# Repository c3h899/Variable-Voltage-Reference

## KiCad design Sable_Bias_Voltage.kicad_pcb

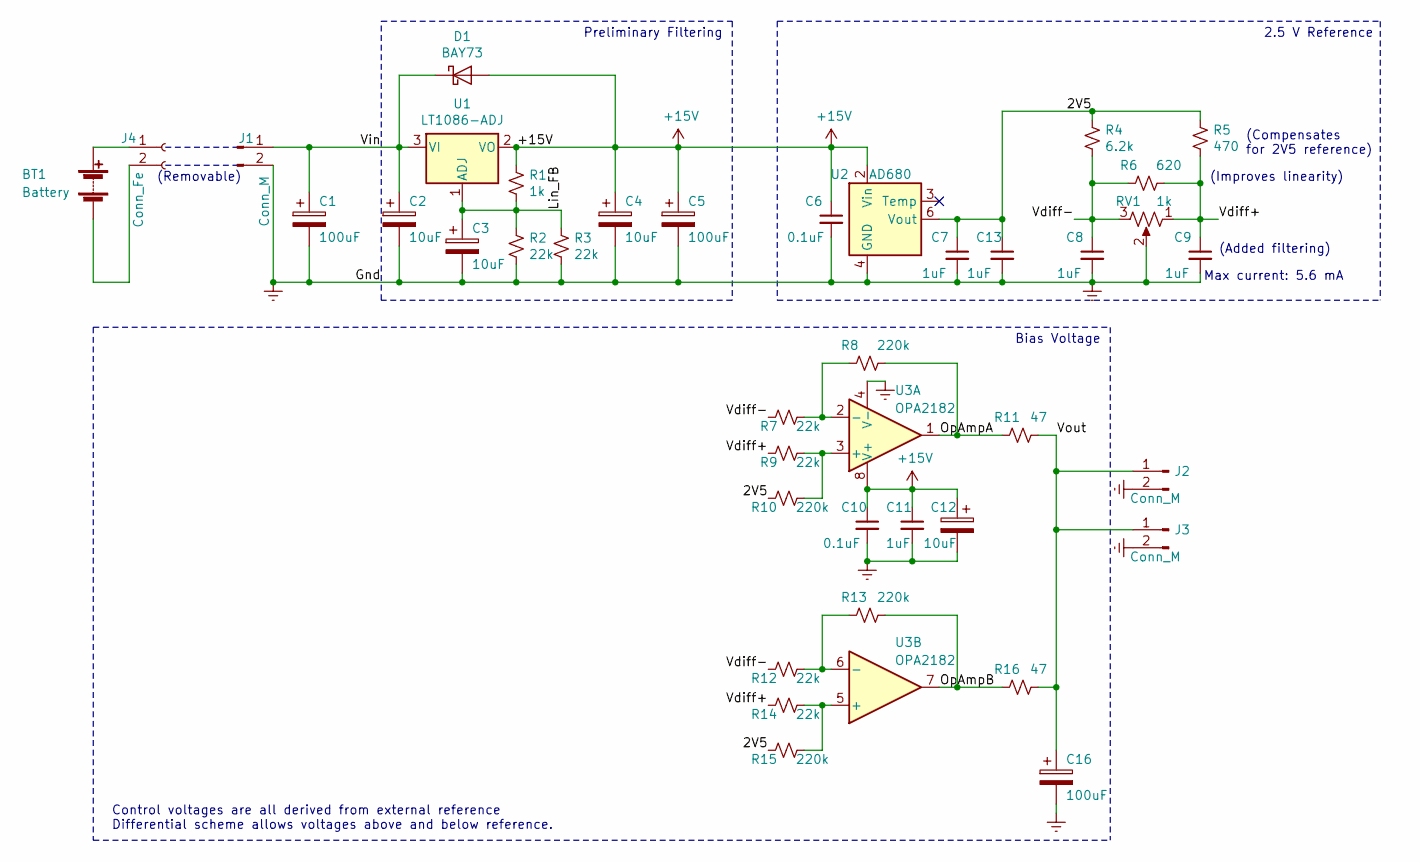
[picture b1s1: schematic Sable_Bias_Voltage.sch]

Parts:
BT1: Battery
C1, C5, C16: 100uF; CP_Radial_D8.0mm_P3.50mm
C2, C3, C4, C12: 10uF; C_Disc_D6.0mm_W4.4mm_P5.00mm
C6, C10: 0.1uF; C_Disc_D6.0mm_W2.5mm_P5.00mm
C7, C8, C9, C11, C13: 1uF; C_Disc_D6.0mm_W2.5mm_P5.00mm
D1: BAY73; D_DO-35_SOD27_P7.62mm_Horizontal
J1, J2, J3: Conn_M; PinHeader_1x02_P2.54mm_Vertical
J4: Conn_Fe
R1: 1k; R_Axial_DIN0204_L3.6mm_D1.6mm_P7.62mm_Horizontal
R2, R3, R7, R9, R12, R14: 22k; R_Axial_DIN0204_L3.6mm_D1.6mm_P7.62mm_Horizontal
R4: 6.2k; R_Axial_DIN0204_L3.6mm_D1.6mm_P7.62mm_Horizontal
R5: 470; R_Axial_DIN0204_L3.6mm_D1.6mm_P7.62mm_Horizontal
R6: 620; R_Axial_DIN0204_L3.6mm_D1.6mm_P7.62mm_Horizontal
R8, R10, R13, R15: 220k; R_Axial_DIN0204_L3.6mm_D1.6mm_P7.62mm_Horizontal
R11, R16: 47; R_Axial_DIN0204_L3.6mm_D1.6mm_P7.62mm_Horizontal
RV1: 1k; Potentiometer_Bourns_3266W_Vertical
U1: LT1086-ADJ; TO-220-3_Vertical
U2: AD680; DIP-8_W7.62mm_LongPads
U3: OPA2182; SOIC-8_3.9x4.9mm_P1.27mm

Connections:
+15V: C4.1, C5.1, C6.1, C10.1, C11.1, C12.1, D1.2 (A), R1.1, U1.2 (VO), U2.2 (Vin), U3.8 (V+)
/2V5: C7.1, C13.1, R4.1, R5.1, R10.2, R15.2, U2.6 (Vout)
/Lin_FB: C3.1, R1.2, R2.1, R3.1, U1.1 (ADJ)
/OpAmpA: R8.1, R11.2, U3.1
/OpAmpB: R13.1, R16.2, U3.7
/Vdiff+: C9.1, R5.2, R6.1, R9.2, R14.2, RV1.1
/Vdiff-: C8.1, R4.2, R6.2, R7.2, R12.2, RV1.3
/Vin: C1.1, C2.1, D1.1 (K), J1.1, U1.3 (VI)
/Vout: C16.1, J2.1, J3.1, R11.1, R16.1
Earth: C1.2, C2.2, C3.2, C4.2, C5.2, C6.2, C7.2, C8.2, C9.2, C10.2, C11.2, C12.2, C13.2, C16.2, J1.2, J2.2, J3.2, R2.2, R3.2, RV1.2, U2.4 (GND), U3.4 (V-)
unnamed: BT1.1 (+), J4.1
unnamed: BT1.2 (-), J4.2
unnamed: R7.1, R8.2, U3.2 (-)
unnamed: R9.1, R10.1, U3.3 (+)
unnamed: R12.1, R13.2, U3.6 (-)
unnamed: R14.1, R15.1, U3.5 (+)

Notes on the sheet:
2.5 V Reference
(Removable)
Preliminary Filtering
(Improves linearity)
(Compensates for 2V5 reference)
(Added filtering)
Max current: 5.6 mA
Control voltages are all derived from external reference Differential scheme allows voltages above and below reference.
Bias Voltage

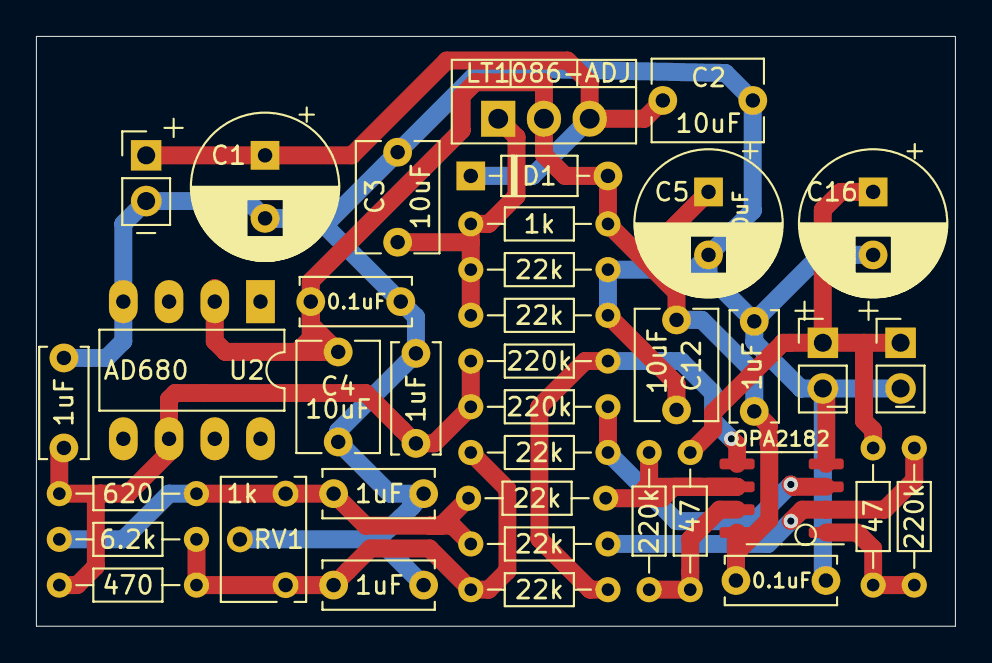
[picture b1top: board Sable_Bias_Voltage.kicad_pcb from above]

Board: 2 copper layers, 51.1 x 32.8 mm, 38 parts (0 on the bottom side), 14 nets.
